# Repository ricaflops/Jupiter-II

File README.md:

# Jupiter-II
**Another Jupiter Ace computer clone**

## Main differences from the original Jupiter Ace
* Buffered composite video output
* Reset button
* Inversed video jumper selection
* Two screen pages and two character sets area (selectable at the video expansion connector)
* Reduced chip count with PLDs replacing several TTL logic
* Additional signals in expansion connectors

For more information on the original Jupiter Ace computer and an extensive software collection visit [The Jupiter Ace Archive](http://jupiter-ace.co.uk/)

## The Jupiter-II Expansion
See the [Jupiter-II Expansion](https://github.com/ricaflops/Jupiter-II-Expansion) project for adding:
- Video Colour
- Programmable Sound Generator
- 128K paged RAM
- Serial Interface
- FORTH vocabulary extension (Color, Memory Paging, Sound Generator, etc.)

# Jumper Settings

Inverse Video Jumper
- Jumper installed: Black text on white background (inversed)
- Jumper removed: White text on black background (default)

ROM image selection Jumper
- Jumper installed: Original Jupiter Ace 8K ROM image
- Jumper removed: Boot with the [Jupiter-II Expansion](https://github.com/ricaflops/Jupiter-II-Expansion)

The original Jupiter Ace 8K ROM image can be found at [The Jupiter Ace Archive](https://www.jupiter-ace.co.uk/).

# Connections

### Power Supply
Connect a 7.5Vdc to 9 Vdc x 1A power supply. Center pin is positive.

### A/V output
- pin 1: Audio Output (BEEP)
- pin 2: Common
- pin 3: Composite Video Output

The video standard is **60Hz NTSC** compatible but converting to 50Hz PAL by recoding the PLDs shall not be too difficult.

### Tape I/O
- pin 1: MIC output (for LOADing)
- pin 2: Common
- pin 3: EAR input (for SAVEing)

### Expansion
50 pin header connector (2x25 female).
Similar layout as the original Jupiter Ace with additional pins "-ROMSL" and "SPEAKER"

* pin 1:**GND** , pin 2:**GND**
* pin 3:**-INT** , pin 4:**GND**
* pin 5:**-NMI** , pin 6:**+9Vdc**
* pin 7:**-HALT** , pin 8:**+5Vdc**
* pin 9:**-MREQ** , pin 10:**-CLK**
* pin 11:**-IORQ** , pin 12:**A11**
* pin 13:**-RD** , pin 14:**A12**
* pin 15:**-WR** , pin 16:**A13**
* pin 17:**-BUSACK** , pin 18:**A14**
* pin 19:**-WAIT** , pin 20:**A15**
* pin 21:**-BUSRQ** , pin 22:**D4**
* pin 23:**-RESET** , pin 24:**D3**
* pin 25:**-M1** , pin 26:**D5**
* pin 27:**-RFSH** , pin 28:**A2**
* pin 29:**A6** , pin 30:**A10**
* pin 31:**A5** , pin 32:**A9**
* pin 33:**A4** , pin 34:**A8**
* pin 35:**A3** , pin 36:**A7**
* pin 37:**A1** , pin 38:**A0**
* pin 39:**D0** , pin 40:**D1**
* pin 41:**D2** , pin 42:**D6**
* pin 43:**D7** , pin 44:**-WE**
* pin 45:(n.c.) , pin 46:(n.c.)
* pin 47:**-ROMSL** , pin 48:**SPEAKER**
* pin 49:(n.c.) , pin 50:(n.c.)

(n.c.) means not connected

**-ROMSL** *(in)* Disables internal ROM chip when connected to +5V

**SPEAKER** *(out)* TTL level Speaker signal (BEEP)

### Video Expansion
30 pins header connector (2x15 female).
Similar layout as the original Jupiter Ace with some additional pins.

* pin 1:**VA3** , pin 2:**VA0**
* pin 3:**VA5** , pin 4:**VA4**
* pin 5:**VD2** , pin 6:**VD3**
* pin 7:**VD1** , pin 8:**VD4**
* pin 9:**VA6** , pin 10:**VD0**
* pin 11:**VA2** , pin 12:**VD7**
* pin 13:**-VRAMWR** , pin 14:**VD5**
* pin 15:**VA8** , pin 16:**VA7**
* pin 17:**VA9** , pin 18:**VA1**
* pin 19:**VD6** , pin 20:**-VLOAD**
* pin 21:**+5Vdc** , pin 22:**GND**
* pin 23:**-CPAGE** , pin 24:**-SPAGE**
* pin 25:**-SCRRAM** , pin 26:**-VSYNC**
* pin 27:**BORDER** , pin 28:**-HSYNC**
* pin 29:**LUMA** , pin 30:**BLANK**

**-VRAMWR** *(out)* Video RAM write enable

**-CPAGE** *(in)* Character Generator page selection

**-SPAGE** *(in)* Screen page selection

**-SCRRAM** *(out)* Screen RAM enabled

**-VSYNC** *(out)* Vertical Video Synch

**-HSYNC** *(out)* Horizontal Video Synch

**LUMA** *(out)* Video Luminance

**BLANK** *(out)* Video Blanking (retrace blanking)

## Tools used & file formats
* Designed with [Kicad](https://www.kicad.org/)
* Programmable Logic Devices coded in CUPL language (compiled with WinCupl available for free at [Microchip](https://www.microchip.com/))

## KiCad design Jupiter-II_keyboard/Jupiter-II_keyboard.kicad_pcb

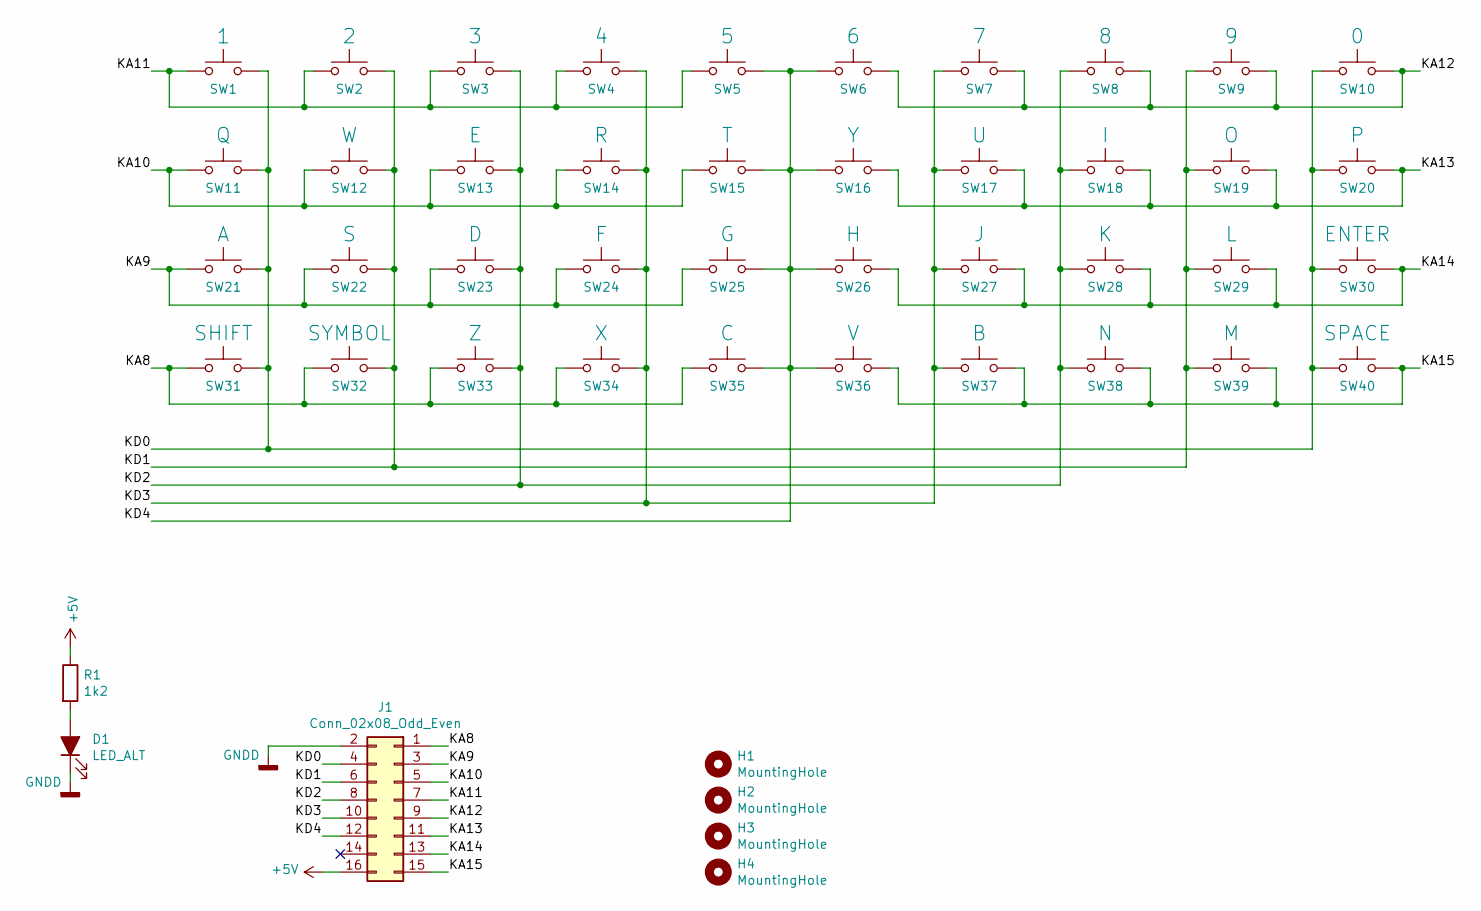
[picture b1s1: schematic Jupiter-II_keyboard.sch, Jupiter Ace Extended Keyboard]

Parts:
D1: LED_ALT; LED_1206_3216Metric_Pad1.42x1.75mm_HandSolder
H1, H2, H3, H4: MountingHole; MountingHole_3.2mm_M3
J1: Conn_02x08_Odd_Even; IDC-Header_2x08_P2.54mm_Vertical
R1: 1k2; R_0805_2012Metric_Pad1.15x1.40mm_HandSolder
SW1: 1; SW_PUSH_6mm
SW2: 2; SW_PUSH_6mm
SW3: 3; SW_PUSH_6mm
SW4: 4; SW_PUSH_6mm
SW5: 5; SW_PUSH_6mm
SW6: 6; SW_PUSH_6mm
SW7: 7; SW_PUSH_6mm
SW8: 8; SW_PUSH_6mm
SW9: 9; SW_PUSH_6mm
SW10: 0; SW_PUSH_6mm
SW11: Q; SW_PUSH_6mm
SW12: W; SW_PUSH_6mm
SW13: E; SW_PUSH_6mm
SW14: R; SW_PUSH_6mm
SW15: T; SW_PUSH_6mm
SW16: Y; SW_PUSH_6mm
SW17: U; SW_PUSH_6mm
SW18: I; SW_PUSH_6mm
SW19: O; SW_PUSH_6mm
SW20: P; SW_PUSH_6mm
SW21: A; SW_PUSH_6mm
SW22: S; SW_PUSH_6mm
SW23: D; SW_PUSH_6mm
SW24: F; SW_PUSH_6mm
SW25: G; SW_PUSH_6mm
SW26: H; SW_PUSH_6mm
SW27: J; SW_PUSH_6mm
SW28: K; SW_PUSH_6mm
SW29: L; SW_PUSH_6mm
SW30: ENTER; SW_PUSH_6mm
SW31: SHIFT; SW_PUSH_6mm
SW32: SYMBOL; SW_PUSH_6mm
SW33: Z; SW_PUSH_6mm
SW34: X; SW_PUSH_6mm
SW35: C; SW_PUSH_6mm
SW36: V; SW_PUSH_6mm
SW37: B; SW_PUSH_6mm
SW38: N; SW_PUSH_6mm
SW39: M; SW_PUSH_6mm
SW40: SPACE; SW_PUSH_6mm

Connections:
+5V: J1.16, R1.1
/KA8: J1.1, SW31.1, SW32.1, SW33.1, SW34.1, SW35.1
/KA9: J1.3, SW21.1, SW22.1, SW23.1, SW24.1, SW25.1
/KA10: J1.5, SW11.1, SW12.1, SW13.1, SW14.1, SW15.1
/KA11: J1.7, SW1.1, SW2.1, SW3.1, SW4.1, SW5.1
/KA12: J1.9, SW6.1, SW7.1, SW8.1, SW9.1, SW10.1
/KA13: J1.11, SW16.1, SW17.1, SW18.1, SW19.1, SW20.1
/KA14: J1.13, SW26.1, SW27.1, SW28.1, SW29.1, SW30.1
/KA15: J1.15, SW36.1, SW37.1, SW38.1, SW39.1, SW40.1
/KD0: J1.4, SW1.2, SW10.2, SW11.2, SW20.2, SW21.2, SW30.2, SW31.2, SW40.2
/KD1: J1.6, SW2.2, SW9.2, SW12.2, SW19.2, SW22.2, SW29.2, SW32.2, SW39.2
/KD2: J1.8, SW3.2, SW8.2, SW13.2, SW18.2, SW23.2, SW28.2, SW33.2, SW38.2
/KD3: J1.10, SW4.2, SW7.2, SW14.2, SW17.2, SW24.2, SW27.2, SW34.2, SW37.2
/KD4: J1.12, SW5.2, SW6.2, SW15.2, SW16.2, SW25.2, SW26.2, SW35.2, SW36.2
GNDD: D1.1 (K), J1.2
unnamed: D1.2 (A), R1.2

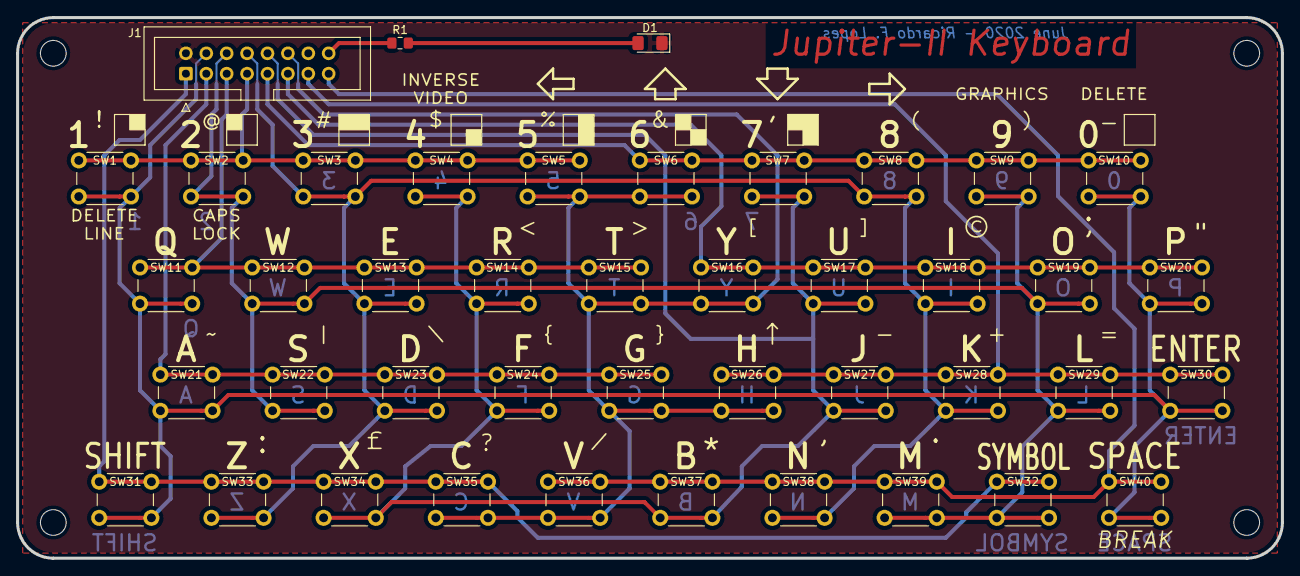
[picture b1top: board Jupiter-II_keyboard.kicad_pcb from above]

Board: 2 copper layers, 157.5 x 67.3 mm, 47 parts (0 on the bottom side), 16 nets.

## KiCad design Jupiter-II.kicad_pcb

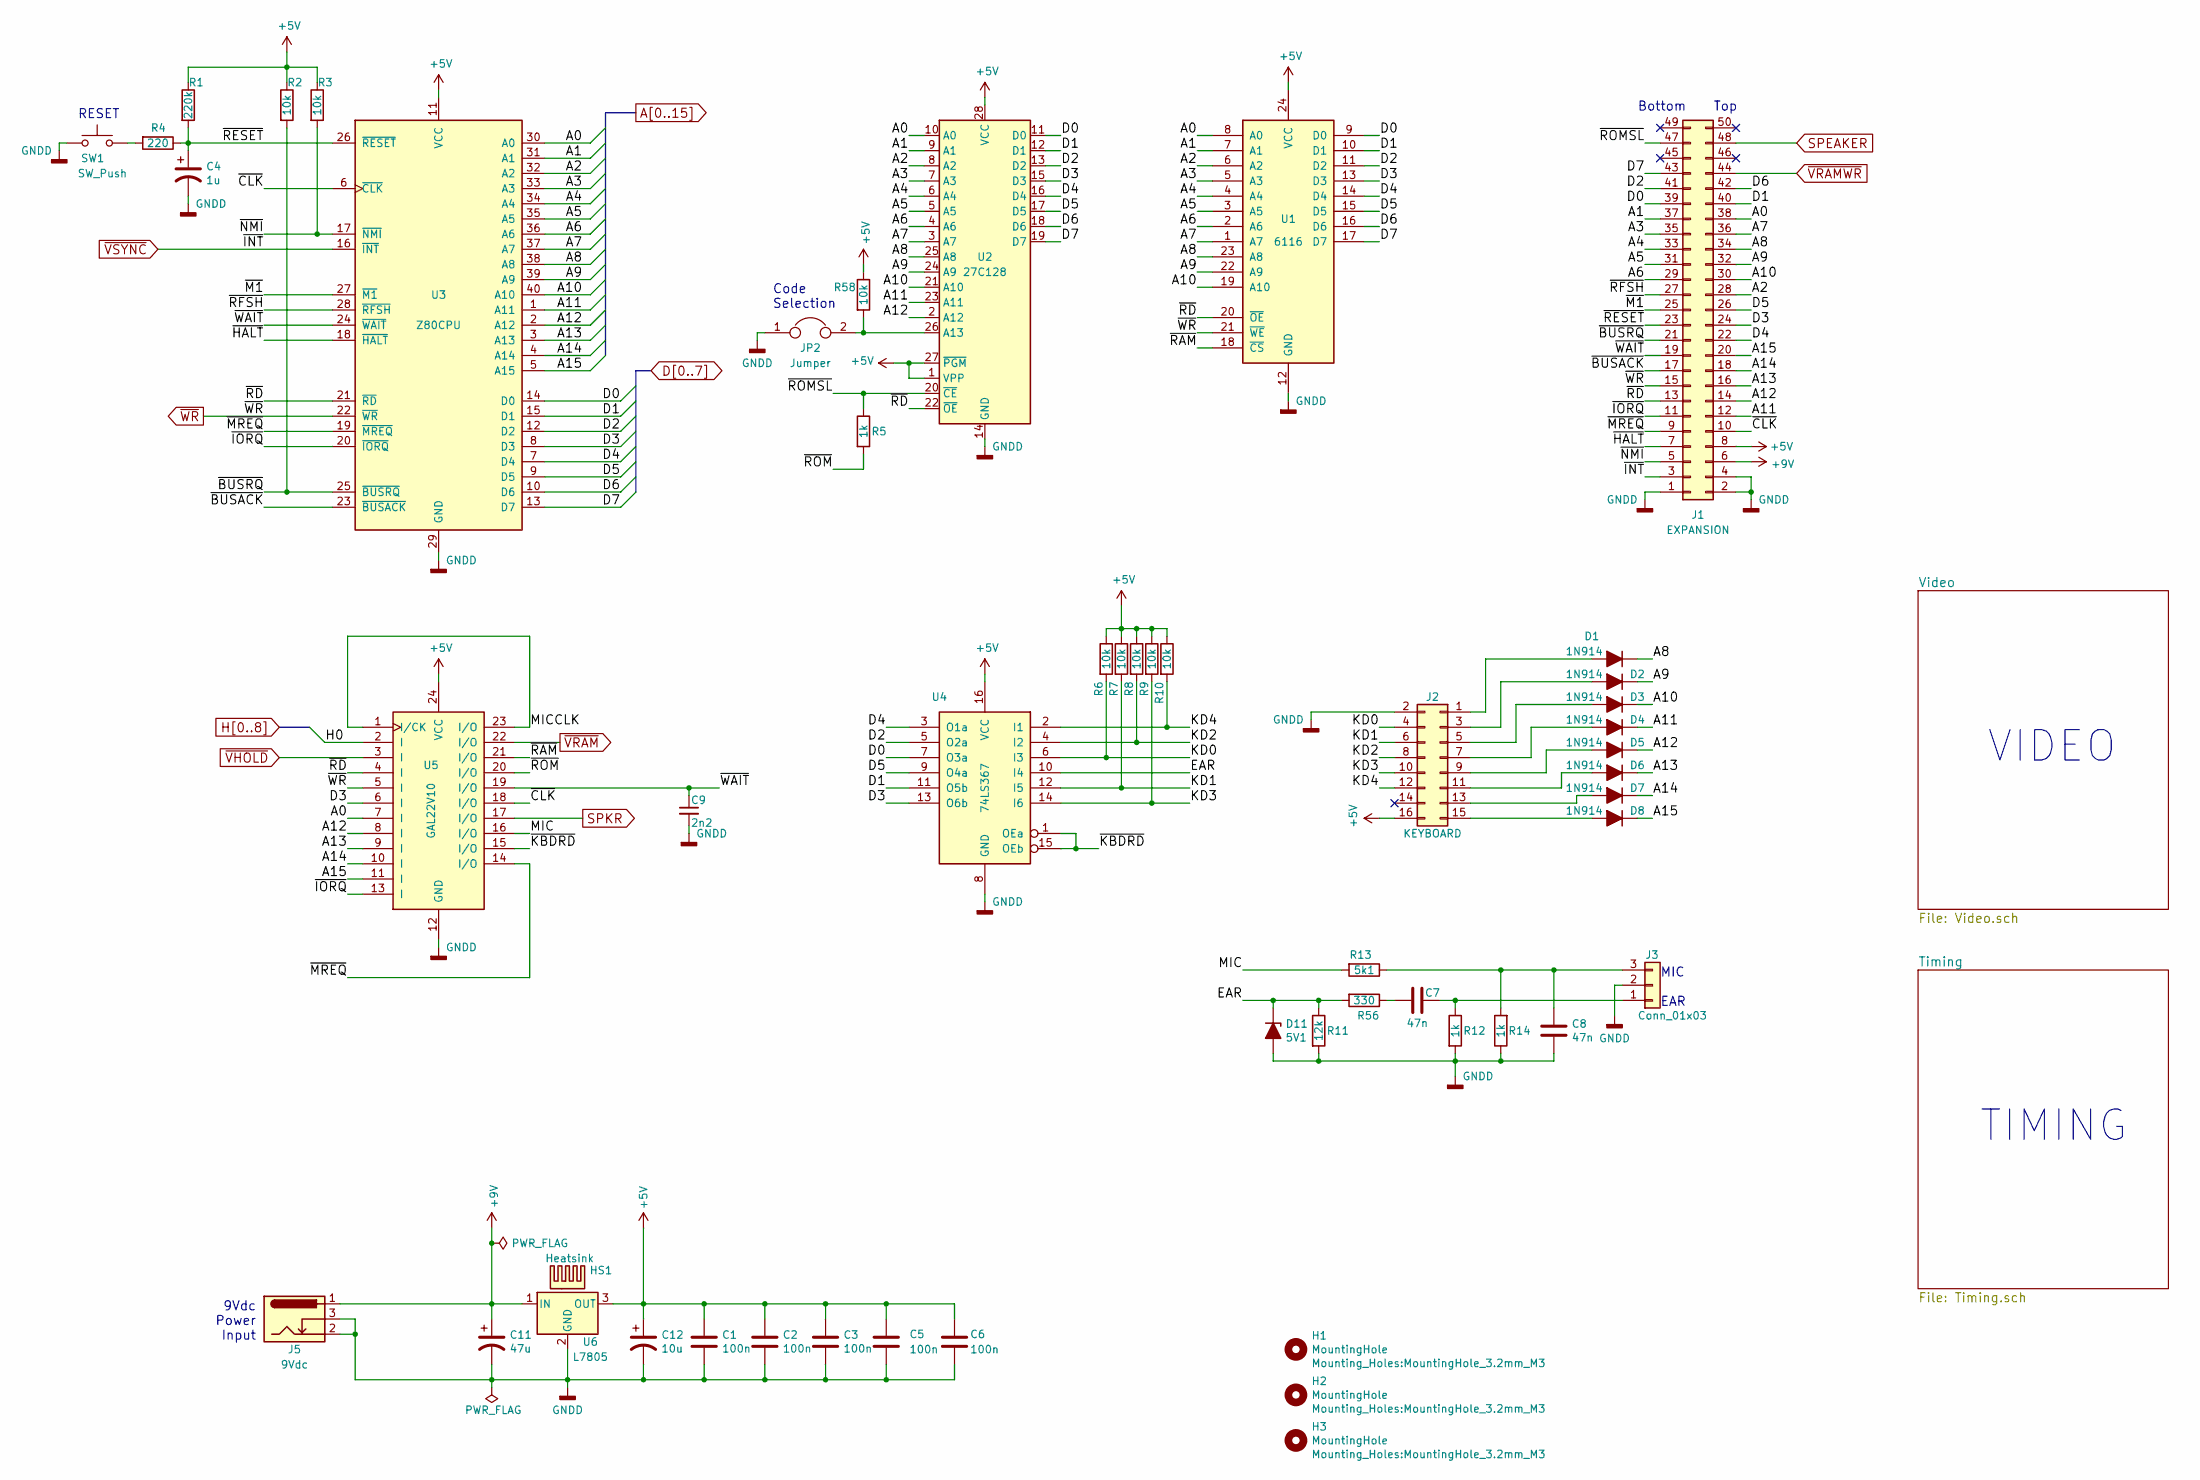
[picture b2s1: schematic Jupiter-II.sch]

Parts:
C1, C2, C3, C5, C6: 100n; C_Rect_L7.0mm_W2.5mm_P5.00mm
C4: 1u; CP_Radial_D6.3mm_P2.50mm
C7, C8: 47n; C_0805_2012Metric_Pad1.15x1.40mm_HandSolder
C9: 2n2; C_0805_2012Metric_Pad1.15x1.40mm_HandSolder
C11: 47u; CP_Radial_D6.3mm_P2.50mm
C12: 10u; CP_Radial_D6.3mm_P2.50mm
D1, D2, D3, D4, D5, D6, D7, D8: 1N914; D_DO-35_SOD27_P7.62mm_Horizontal
D11: 5V1; D_DO-35_SOD27_P2.54mm_Vertical_KathodeUp
H1, H2, H3: MountingHole; MountingHole_3.2mm_M3
HS1: Heatsink; Heatsink_35x12mm_2xFixation1.5mm
J1: EXPANSION; Socket_Strip_Straight_2x25_Pitch2.54mm
J2: KEYBOARD; Multicomp_MC9A12-1634_2x08x2.54mm_Straight
J3: Conn_01x03; Pin_Header_Angled_1x03_Pitch2.54mm
J5: 9Vdc; BarrelJack_Horizontal
JP2: Jumper; PinHeader_1x02_P2.54mm_Vertical
R1: 220k; R_0805_2012Metric_Pad1.15x1.40mm_HandSolder
R2, R3, R6, R7, R8, R9, R10, R58: 10k; R_0805_2012Metric_Pad1.15x1.40mm_HandSolder
R4: 220; R_0805_2012Metric_Pad1.15x1.40mm_HandSolder
R5, R12, R14: 1k; R_0805_2012Metric_Pad1.15x1.40mm_HandSolder
R11: 12k; R_0805_2012Metric_Pad1.15x1.40mm_HandSolder
R13: 5k1; R_0805_2012Metric_Pad1.15x1.40mm_HandSolder
R56: 330; R_0805_2012Metric_Pad1.15x1.40mm_HandSolder
SW1: SW_Push; SW_Tactile_SPST_Angled_PTS645Vx58-2LFS
U1: 6116; DIP-24_W15.24mm_Socket
U2: 27C128; DIP-28_W15.24mm
U3: Z80CPU; DIP-40_W15.24mm_Socket
U4: 74LS367; DIP-16_W7.62mm
U5: GAL22V10; DIP-24_W7.62mm_Socket
U6: L7805; TO-220-3_Vertical

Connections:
+5V: C1.1, C2.1, C3.1, C5.1, C6.1, C12.1, J1.8, J2.16, R1.1, R2.1, R3.1, R6.1, R7.1, R8.1, R9.1, R10.1, R58.1, U1.24 (VCC), U2.1 (VPP), U2.27 (~PGM), U2.28 (VCC), U3.11 (VCC), U4.16 (VCC), U5.24 (VCC), U6.3 (OUT); also elsewhere on the board
+9V: C11.1, J1.6, J5.1, U6.1 (IN)
/EAR: D11.1 (K), R11.1, R56.2, U4.10 (I4)
/KD0: J2.4, R6.2, U4.6 (I3)
/KD1: J2.6, R7.2, U4.12 (I5)
/KD2: J2.8, R8.2, U4.4 (I2)
/KD3: J2.10, R9.2, U4.14 (I6)
/KD4: J2.12, R10.2, U4.2 (I1)
/MIC: R13.2, U5.16 (I/O)
/MICCLK: U5.1 (I/CK), U5.23 (I/O)
/~BUSACK: J1.17, U3.23 (~BUSACK~)
/~BUSRQ: J1.21, R2.2, U3.25 (~BUSRQ~)
/~CLK: J1.10, U3.6 (~CLK~), U5.18 (I/O)
/~HALT: J1.7, U3.18 (~HALT~)
/~IORQ: J1.11, U3.20 (~IORQ~), U5.13 (I)
/~KBDRD: U4.1 (OEa), U4.15 (OEb), U5.15 (I/O)
/~M1: J1.25, U3.27 (~M1~)
/~MREQ: J1.9, U3.19 (~MREQ~), U5.14 (I/O)
/~NMI: J1.5, R3.2, U3.17 (~NMI~)
/~RAM: U1.18 (~CS), U5.21 (I/O)
/~RD: J1.13, U1.20 (~OE), U2.22 (~OE), U3.21 (~RD~), U5.4 (I)
/~RESET: C4.1, J1.23, R1.2, R4.1, U3.26 (~RESET~)
/~RFSH: J1.27, U3.28 (~RFSH~)
/~ROM: R5.2, U5.20 (I/O)
/~ROMSL: J1.47, R5.1, U2.20 (~CE)
/~WAIT: C9.1, J1.19, U3.24 (~WAIT~), U5.19 (I/O)
A0: J1.38, U1.8 (A0), U2.10 (A0), U3.30 (A0), U5.7 (I); also elsewhere on the board
A1: J1.37, U1.7 (A1), U2.9 (A1), U3.31 (A1); also elsewhere on the board
A2: J1.28, U1.6 (A2), U2.8 (A2), U3.32 (A2); also elsewhere on the board
A3: J1.35, U1.5 (A3), U2.7 (A3), U3.33 (A3); also elsewhere on the board
A4: J1.33, U1.4 (A4), U2.6 (A4), U3.34 (A4); also elsewhere on the board
A5: J1.31, U1.3 (A5), U2.5 (A5), U3.35 (A5); also elsewhere on the board
A6: J1.29, U1.2 (A6), U2.4 (A6), U3.36 (A6); also elsewhere on the board
A7: J1.36, U1.1 (A7), U2.3 (A7), U3.37 (A7); also elsewhere on the board
A8: D1.1 (K), J1.34, U1.23 (A8), U2.25 (A8), U3.38 (A8); also elsewhere on the board
A9: D2.1 (K), J1.32, U1.22 (A9), U2.24 (A9), U3.39 (A9); also elsewhere on the board
A10: D3.1 (K), J1.30, U1.19 (A10), U2.21 (A10), U3.40 (A10); also elsewhere on the board
A11: D4.1 (K), J1.12, U2.23 (A11), U3.1 (A11); also elsewhere on the board
A12: D5.1 (K), J1.14, U2.2 (A12), U3.2 (A12), U5.8 (I)
A13: D6.1 (K), J1.16, U3.3 (A13), U5.9 (I)
A14: D7.1 (K), J1.18, U3.4 (A14), U5.10 (I)
A15: D8.1 (K), J1.20, U3.5 (A15), U5.11 (I)
D0: J1.39, U1.9 (D0), U2.11 (D0), U3.14 (D0), U4.7 (O3a); also elsewhere on the board
D1: J1.40, U1.10 (D1), U2.12 (D1), U3.15 (D1), U4.11 (O5b); also elsewhere on the board
D2: J1.41, U1.11 (D2), U2.13 (D2), U3.12 (D2), U4.5 (O2a); also elsewhere on the board
D3: J1.24, U1.13 (D3), U2.15 (D3), U3.8 (D3), U4.13 (O6b), U5.6 (I); also elsewhere on the board
D4: J1.22, U1.14 (D4), U2.16 (D4), U3.7 (D4), U4.3 (O1a); also elsewhere on the board
D5: J1.26, U1.15 (D5), U2.17 (D5), U3.9 (D5), U4.9 (O4a); also elsewhere on the board
D6: J1.42, U1.16 (D6), U2.18 (D6), U3.10 (D6); also elsewhere on the board
D7: J1.43, U1.17 (D7), U2.19 (D7), U3.13 (D7); also elsewhere on the board
GNDD: C1.2, C2.2, C3.2, C4.2, C5.2, C6.2, C8.2, C9.2, C11.2, C12.2, D11.2 (A), J1.1, J1.2, J1.4, J2.2, J3.2, J5.2, J5.3, JP2.1, R11.2, R12.2, R14.1, SW1.1, U1.12 (GND), U2.14 (GND), U3.29 (GND), U4.8 (GND), U5.12 (GND), U6.2 (GND); also elsewhere on the board
H0: U5.2 (I); also elsewhere on the board
unnamed: C7.1, J3.1, R12.1
unnamed: C7.2, R56.1
unnamed: C8.1, J3.3, R13.1, R14.2
unnamed: D1.2 (A), J2.1
unnamed: D2.2 (A), J2.3
unnamed: D3.2 (A), J2.5
unnamed: D4.2 (A), J2.7
unnamed: D5.2 (A), J2.9
unnamed: D6.2 (A), J2.11
unnamed: D7.2 (A), J2.13
unnamed: D8.2 (A), J2.15
unnamed: JP2.2, R58.2, U2.26 (A13)
unnamed: R4.2, SW1.2
SPEAKER: J1.48; also elsewhere on the board
SPKR: U5.17 (I/O); also elsewhere on the board
~VHOLD: U5.3 (I); also elsewhere on the board
~VRAM: U5.22 (I/O); also elsewhere on the board
~VRAMWR: J1.44; also elsewhere on the board
~VSYNC: J1.3, U3.16 (~INT~); also elsewhere on the board
~WR: J1.15, U1.21 (~WE), U3.22 (~WR~), U5.5 (I); also elsewhere on the board

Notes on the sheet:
RESET
TIMING
VIDEO
Bottom Top
9Vdc Power Input
MIC EAR
Code Selection

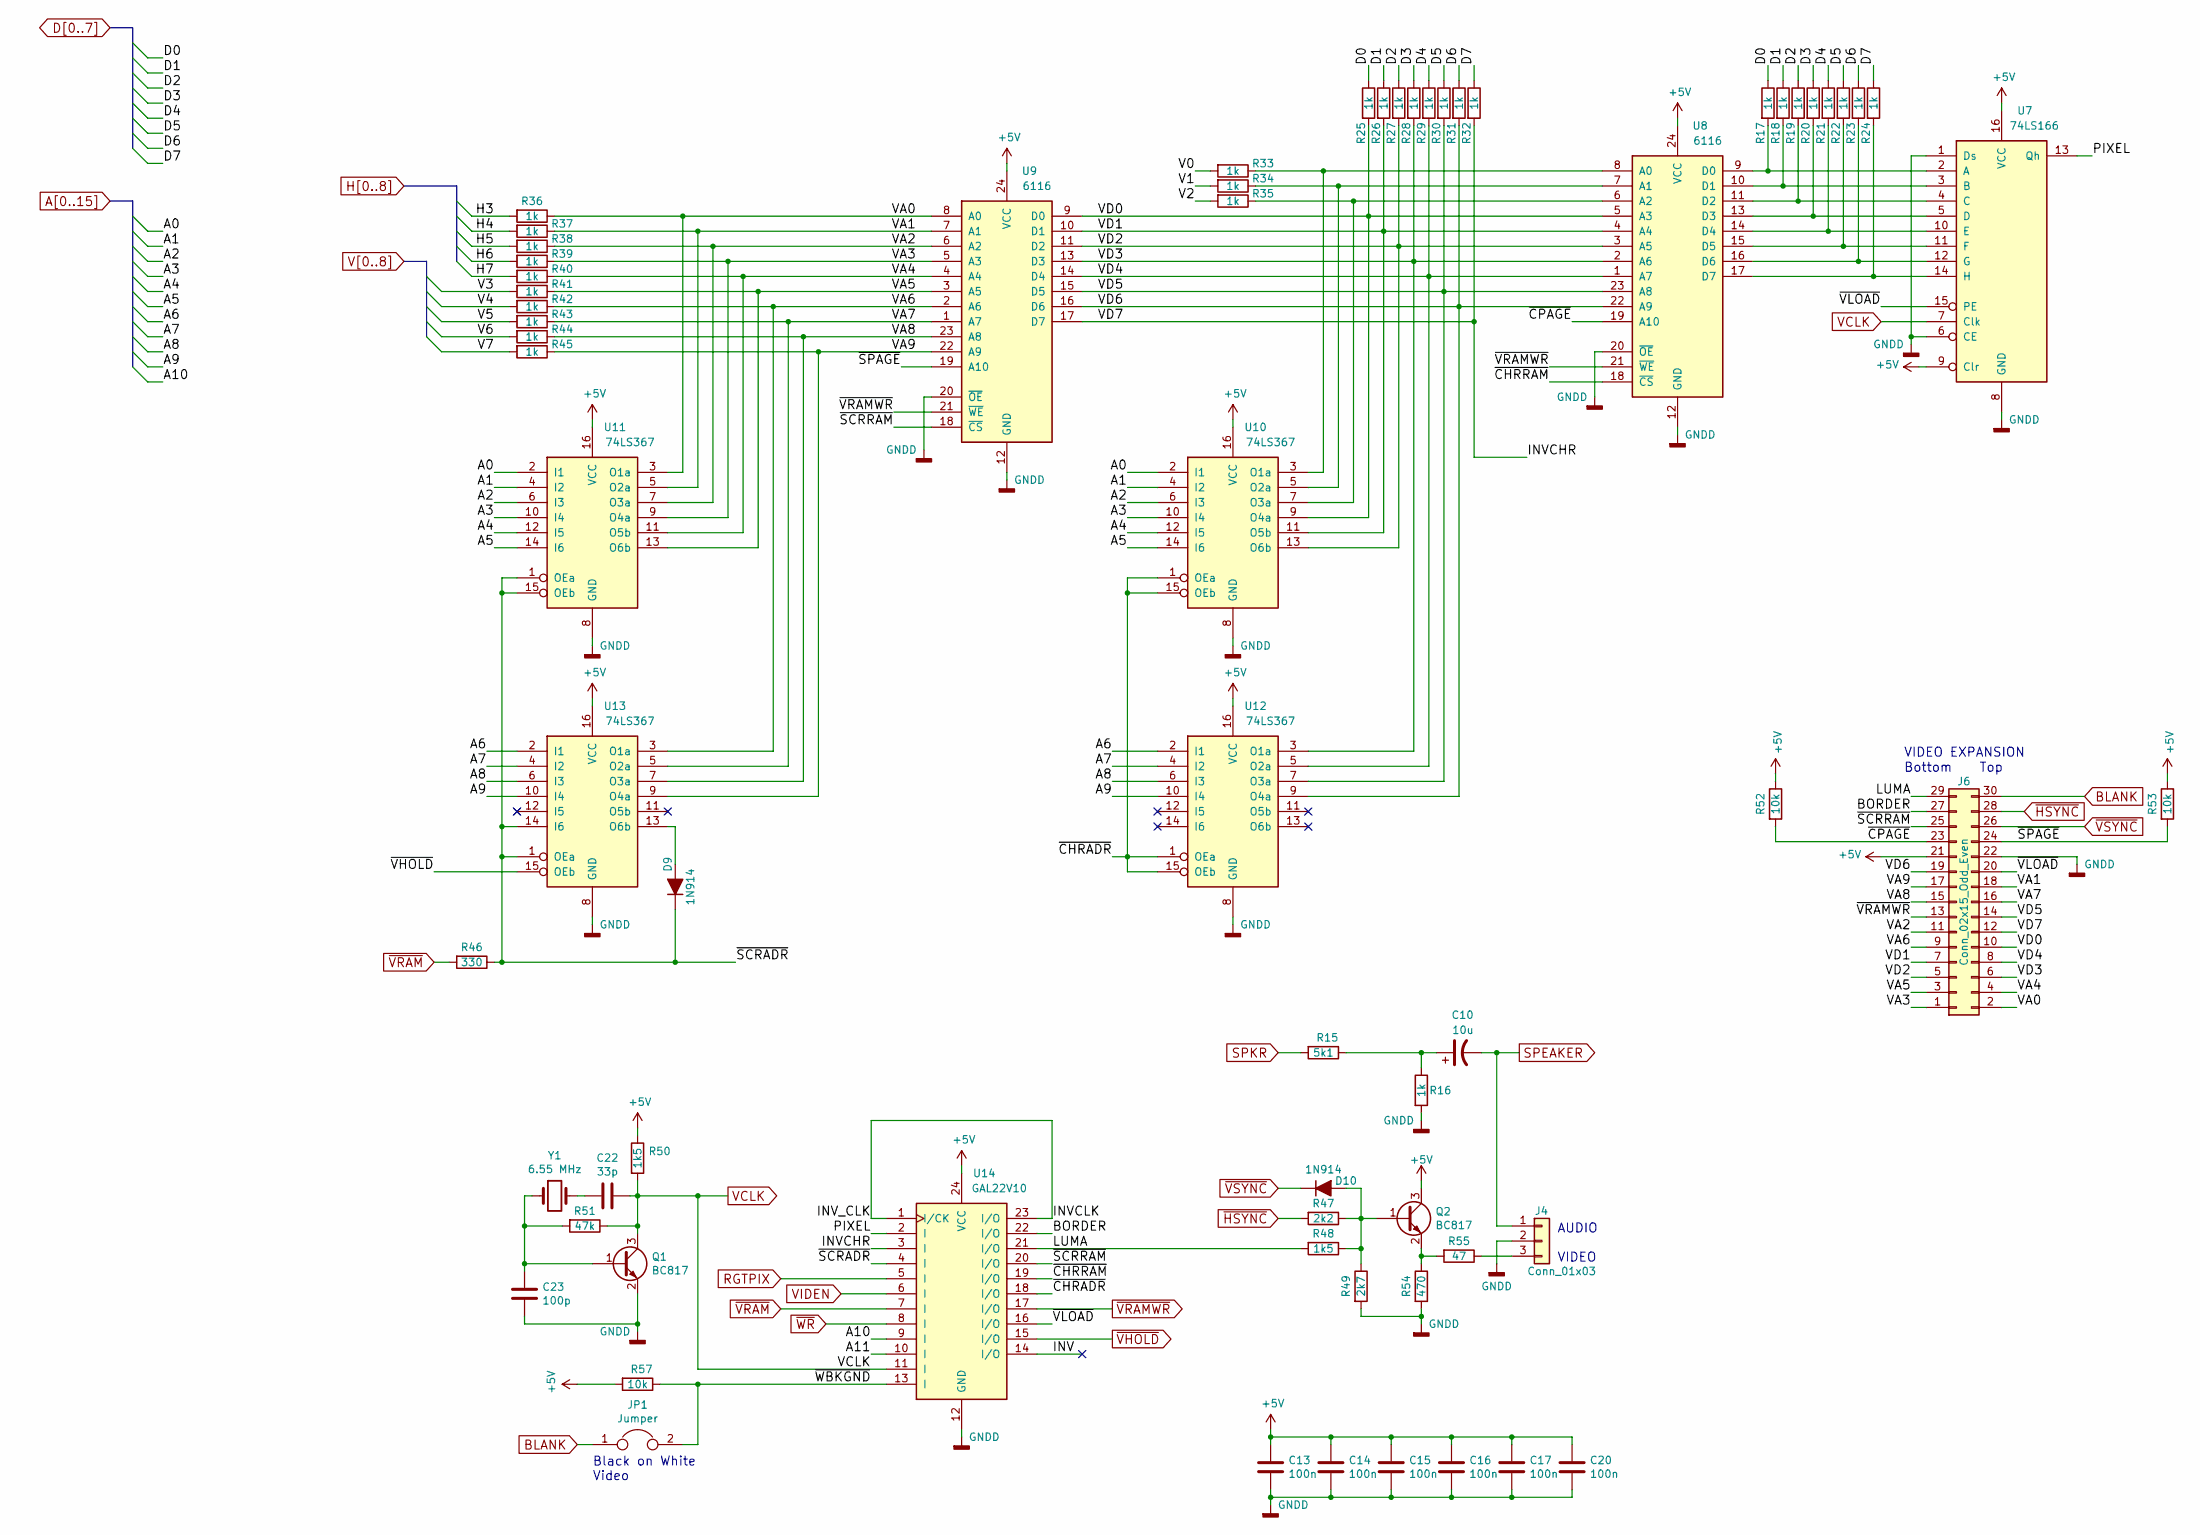
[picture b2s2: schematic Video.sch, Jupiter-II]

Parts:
C10: 10u; CP_Radial_D6.3mm_P2.50mm
C13, C14, C15, C16, C17, C20: 100n; C_Rect_L7.0mm_W2.5mm_P5.00mm
C22: 33p; C_0805_2012Metric_Pad1.15x1.40mm_HandSolder
C23: 100p; C_0805_2012Metric_Pad1.15x1.40mm_HandSolder
D9, D10: 1N914; D_DO-35_SOD27_P7.62mm_Horizontal
J4: Conn_01x03; Molex_KK-6410-03_03x2.54mm_Straight
J6: Conn_02x15_Odd_Even; Socket_Strip_Straight_2x15_Pitch2.54mm
JP1: Jumper; Pin_Header_Straight_1x02_Pitch2.54mm
Q1, Q2: BC817; SOT-23
R15: 5k1; R_0805_2012Metric_Pad1.15x1.40mm_HandSolder
R16, R17, R18, R19, R20, R21, R22, R23, R24, R25, R26, R27, R28, R29, R30, R31, R32, R33, R34, R35, R36, R37, R38, R39, R40, R41, R42, R43, R44, R45: 1k; R_0805_2012Metric_Pad1.15x1.40mm_HandSolder
R46: 330; R_0805_2012Metric_Pad1.15x1.40mm_HandSolder
R47: 2k2; R_0805_2012Metric_Pad1.15x1.40mm_HandSolder
R48, R50: 1k5; R_0805_2012Metric_Pad1.15x1.40mm_HandSolder
R49: 2k7; R_0805_2012Metric_Pad1.15x1.40mm_HandSolder
R51: 47k; R_0805_2012Metric_Pad1.15x1.40mm_HandSolder
R52, R53, R57: 10k; R_0805_2012Metric_Pad1.15x1.40mm_HandSolder
R54: 470; R_0805_2012Metric_Pad1.15x1.40mm_HandSolder
R55: 47; R_0805_2012Metric_Pad1.15x1.40mm_HandSolder
U7: 74LS166; DIP-16_W7.62mm
U8, U9: 6116; DIP-24_W15.24mm_Socket
U10, U11, U12, U13: 74LS367; DIP-16_W7.62mm
U14: GAL22V10; DIP-24_W7.62mm_Socket
Y1: 6.55 MHz; Crystal_HC18-U_Vertical

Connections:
+5V: C13.1, C14.1, C15.1, C16.1, C17.1, C20.1, J6.21, Q2.3 (C), R50.1, R52.1, R53.1, R57.2, U7.9 (Clr), U7.16 (VCC), U8.24 (VCC), U9.24 (VCC), U10.16 (VCC), U11.16 (VCC), U12.16 (VCC), U13.16 (VCC), U14.24 (VCC); also elsewhere on the board
/Video/BORDER: J6.27, U14.22 (I/O)
/Video/INV: U14.14 (I/O)
/Video/INVCHR: J6.12, R32.2, U9.17 (D7), U14.3 (I)
/Video/INVCLK: U14.1 (I/CK), U14.23 (I/O)
/Video/LUMA: J6.29, R48.2, U14.21 (I/O)
/Video/PIXEL: U7.13 (Qh), U14.2 (I)
/Video/VA0: J6.2, R36.1, U9.8 (A0), U11.3 (O1a)
/Video/VA1: J6.18, R37.1, U9.7 (A1), U11.5 (O2a)
/Video/VA2: J6.11, R38.1, U9.6 (A2), U11.7 (O3a)
/Video/VA3: J6.1, R39.1, U9.5 (A3), U11.9 (O4a)
/Video/VA4: J6.4, R40.1, U9.4 (A4), U11.11 (O5b)
/Video/VA5: J6.3, R41.1, U9.3 (A5), U11.13 (O6b)
/Video/VA6: J6.9, R42.1, U9.2 (A6), U13.3 (O1a)
/Video/VA7: J6.16, R43.1, U9.1 (A7), U13.5 (O2a)
/Video/VA8: J6.15, R44.1, U9.23 (A8), U13.7 (O3a)
/Video/VA9: J6.17, R45.1, U9.22 (A9), U13.9 (O4a)
/Video/VD0: J6.10, R25.2, U8.5 (A3), U9.9 (D0), U10.9 (O4a)
/Video/VD1: J6.7, R26.2, U8.4 (A4), U9.10 (D1), U10.11 (O5b)
/Video/VD2: J6.5, R27.2, U8.3 (A5), U9.11 (D2), U10.13 (O6b)
/Video/VD3: J6.6, R28.2, U8.2 (A6), U9.13 (D3), U12.3 (O1a)
/Video/VD4: J6.8, R29.2, U8.1 (A7), U9.14 (D4), U12.5 (O2a)
/Video/VD5: J6.14, R30.2, U8.23 (A8), U9.15 (D5), U12.7 (O3a)
/Video/VD6: J6.19, R31.2, U8.22 (A9), U9.16 (D6), U12.9 (O4a)
/Video/~CHRADR: U10.1 (OEa), U10.15 (OEb), U12.1 (OEa), U12.15 (OEb), U14.18 (I/O)
/Video/~CHRRAM: U8.18 (~CS), U14.19 (I/O)
/Video/~CPAGE: J6.23, R52.2, U8.19 (A10)
/Video/~SCRADR: D9.1 (K), R46.1, U11.1 (OEa), U11.15 (OEb), U13.1 (OEa), U13.14 (I6), U14.4 (I)
/Video/~SCRRAM: J6.25, U9.18 (~CS), U14.20 (I/O)
/Video/~SPAGE: J6.24, R53.2, U9.19 (A10)
/Video/~VLOAD: J6.20, U7.15 (PE), U14.16 (I/O)
/Video/~WBKGND: JP1.2, R57.1, U14.13 (I)
A0: U10.2 (I1), U11.2 (I1); also elsewhere on the board
A1: U10.4 (I2), U11.4 (I2); also elsewhere on the board
A2: U10.6 (I3), U11.6 (I3); also elsewhere on the board
A3: U10.10 (I4), U11.10 (I4); also elsewhere on the board
A4: U10.12 (I5), U11.12 (I5); also elsewhere on the board
A5: U10.14 (I6), U11.14 (I6); also elsewhere on the board
A6: U12.2 (I1), U13.2 (I1); also elsewhere on the board
A7: U12.4 (I2), U13.4 (I2); also elsewhere on the board
A8: U12.6 (I3), U13.6 (I3); also elsewhere on the board
A9: U12.10 (I4), U13.10 (I4); also elsewhere on the board
A10: U14.9 (I); also elsewhere on the board
A11: U14.10 (I); also elsewhere on the board
BLANK: J6.30, JP1.1; also elsewhere on the board
D0: R17.1, R25.1; also elsewhere on the board
D1: R18.1, R26.1; also elsewhere on the board
D2: R19.1, R27.1; also elsewhere on the board
D3: R20.1, R28.1; also elsewhere on the board
D4: R21.1, R29.1; also elsewhere on the board
D5: R22.1, R30.1; also elsewhere on the board
D6: R23.1, R31.1; also elsewhere on the board
D7: R24.1, R32.1; also elsewhere on the board
GNDD: C13.2, C14.2, C15.2, C16.2, C17.2, C20.2, C23.2, J4.2, J6.22, Q1.2 (E), R16.2, R49.2, R54.2, U7.1 (Ds), U7.6 (CE), U7.8 (GND), U8.12 (GND), U8.20 (~OE), U9.12 (GND), U9.20 (~OE), U10.8 (GND), U11.8 (GND), U12.8 (GND), U13.8 (GND), U14.12 (GND); also elsewhere on the board
H3: R36.2; also elsewhere on the board
H4: R37.2; also elsewhere on the board
H5: R38.2; also elsewhere on the board
H6: R39.2; also elsewhere on the board
H7: R40.2; also elsewhere on the board
unnamed: C10.1, R15.1, R16.1
unnamed: C22.2, Y1.2
unnamed: C23.1, Q1.1 (B), R51.2, Y1.1
unnamed: D9.2 (A), U13.13 (O6b)
unnamed: D10.2 (A), Q2.1 (B), R47.1, R48.1, R49.1
unnamed: J4.3, R55.1
unnamed: Q2.2 (E), R54.1, R55.2
unnamed: R17.2, U7.2 (A), U8.9 (D0)
unnamed: R18.2, U7.3 (B), U8.10 (D1)
unnamed: R19.2, U7.4 (C), U8.11 (D2)
unnamed: R20.2, U7.5 (D), U8.13 (D3)
unnamed: R21.2, U7.10 (E), U8.14 (D4)
unnamed: R22.2, U7.11 (F), U8.15 (D5)
unnamed: R23.2, U7.12 (G), U8.16 (D6)
unnamed: R24.2, U7.14 (H), U8.17 (D7)
unnamed: R33.1, U8.8 (A0), U10.3 (O1a)
unnamed: R34.1, U8.7 (A1), U10.5 (O2a)
unnamed: R35.1, U8.6 (A2), U10.7 (O3a)
RGTPIX: U14.5 (I); also elsewhere on the board
SPEAKER: C10.2, J4.1; also elsewhere on the board
SPKR: R15.2; also elsewhere on the board
V0: R33.2; also elsewhere on the board
V1: R34.2; also elsewhere on the board
V2: R35.2; also elsewhere on the board
V3: R41.2; also elsewhere on the board
V4: R42.2; also elsewhere on the board
V5: R43.2; also elsewhere on the board
V6: R44.2; also elsewhere on the board
V7: R45.2; also elsewhere on the board
VCLK: C22.1, Q1.3 (C), R50.2, R51.1, U7.7 (Clk), U14.11 (I); also elsewhere on the board
VIDEN: U14.6 (I); also elsewhere on the board
~HSYNC: J6.28, R47.2; also elsewhere on the board
~VHOLD: U13.15 (OEb), U14.15 (I/O); also elsewhere on the board
~VRAM: R46.2, U14.7 (I); also elsewhere on the board
~VRAMWR: J6.13, U8.21 (~WE), U9.21 (~WE), U14.17 (I/O); also elsewhere on the board
~VSYNC: D10.1 (K), J6.26; also elsewhere on the board
~WR: U14.8 (I); also elsewhere on the board

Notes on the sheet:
AUDIO VIDEO
Bottom Top
VIDEO EXPANSION
Black on White Video

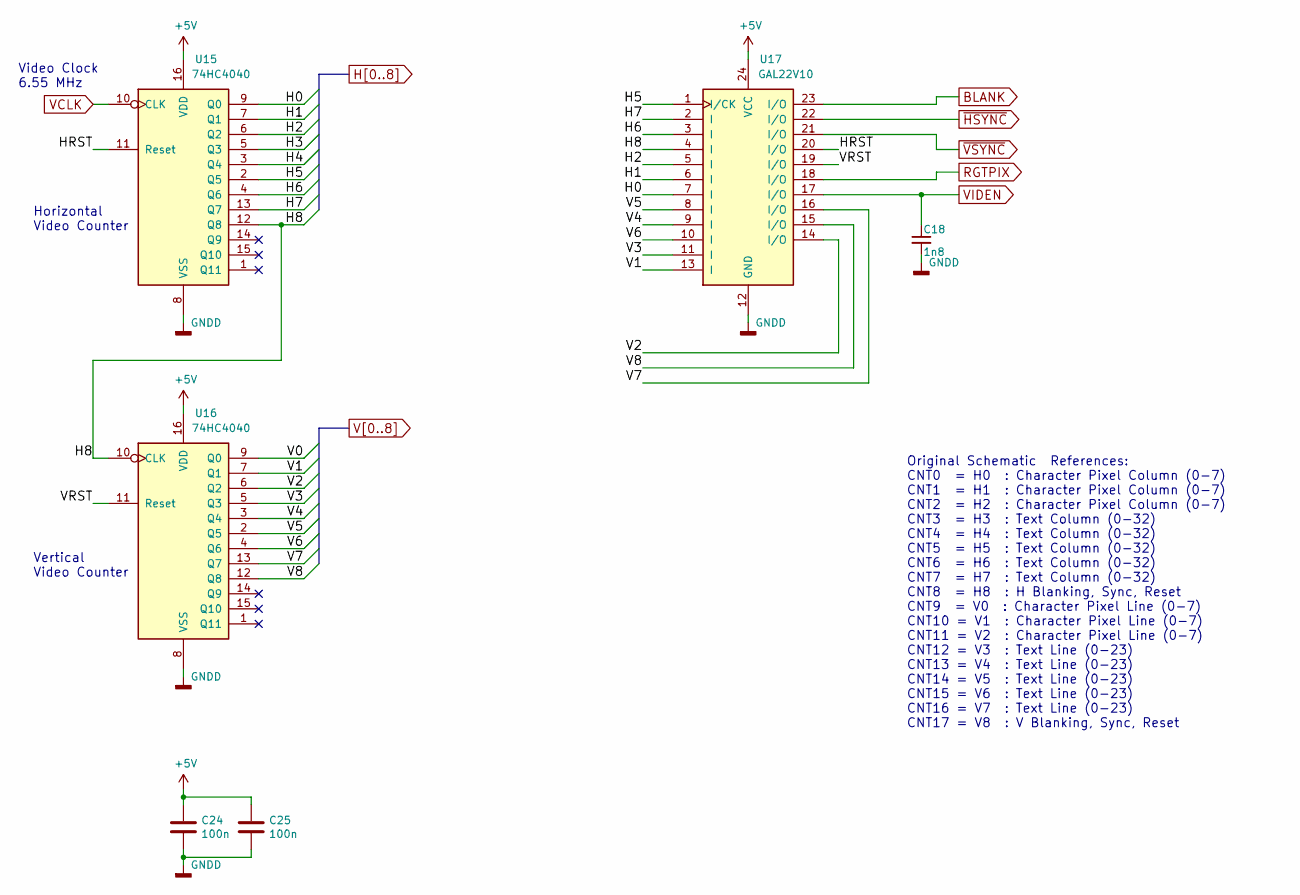
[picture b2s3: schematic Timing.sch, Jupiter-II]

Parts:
C18: 1n8; C_0805_2012Metric_Pad1.15x1.40mm_HandSolder
C24, C25: 100n; C_Rect_L7.0mm_W2.5mm_P5.00mm
U15, U16: 74HC4040; DIP-16_W7.62mm
U17: GAL22V10; DIP-24_W7.62mm_Socket

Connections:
+5V: C24.1, C25.1, U15.16 (VDD), U16.16 (VDD), U17.24 (VCC); also elsewhere on the board
/Timing/HRST: U15.11 (Reset), U17.20 (I/O)
/Timing/VRST: U16.11 (Reset), U17.19 (I/O)
BLANK: U17.23 (I/O); also elsewhere on the board
GNDD: C18.2, C24.2, C25.2, U15.8 (VSS), U16.8 (VSS), U17.12 (GND); also elsewhere on the board
H0: U15.9 (Q0), U17.7 (I); also elsewhere on the board
H1: U15.7 (Q1), U17.6 (I)
H2: U15.6 (Q2), U17.5 (I)
H3: U15.5 (Q3); also elsewhere on the board
H4: U15.3 (Q4); also elsewhere on the board
H5: U15.2 (Q5), U17.1 (I/CK); also elsewhere on the board
H6: U15.4 (Q6), U17.3 (I); also elsewhere on the board
H7: U15.13 (Q7), U17.2 (I); also elsewhere on the board
H8: U15.12 (Q8), U16.10 (CLK), U17.4 (I)
RGTPIX: U17.18 (I/O); also elsewhere on the board
V0: U16.9 (Q0); also elsewhere on the board
V1: U16.7 (Q1), U17.13 (I); also elsewhere on the board
V2: U16.6 (Q2), U17.14 (I/O); also elsewhere on the board
V3: U16.5 (Q3), U17.11 (I); also elsewhere on the board
V4: U16.3 (Q4), U17.9 (I); also elsewhere on the board
V5: U16.2 (Q5), U17.8 (I); also elsewhere on the board
V6: U16.4 (Q6), U17.10 (I); also elsewhere on the board
V7: U16.13 (Q7), U17.16 (I/O); also elsewhere on the board
V8: U16.12 (Q8), U17.15 (I/O)
VCLK: U15.10 (CLK); also elsewhere on the board
VIDEN: C18.1, U17.17 (I/O); also elsewhere on the board
~HSYNC: U17.22 (I/O); also elsewhere on the board
~VSYNC: U17.21 (I/O); also elsewhere on the board

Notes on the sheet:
Video Clock 6.55 MHz
Horizontal Video Counter
Vertical Video Counter
Original Schematic References: CNT0 = H0 : Character Pixel Column (0-7) CNT1 = H1 : Character Pixel Column (0-7) CNT2 = H2 : Character Pixel Column (0-7) CNT3 = H3 : Text Column (0-32) CNT4 = H4 : Text Column (0-32) CNT5 = H5 : Text Column (0-32) CNT6 = H6 : Text Column (0-32) CNT7 = H7 : Text Colu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

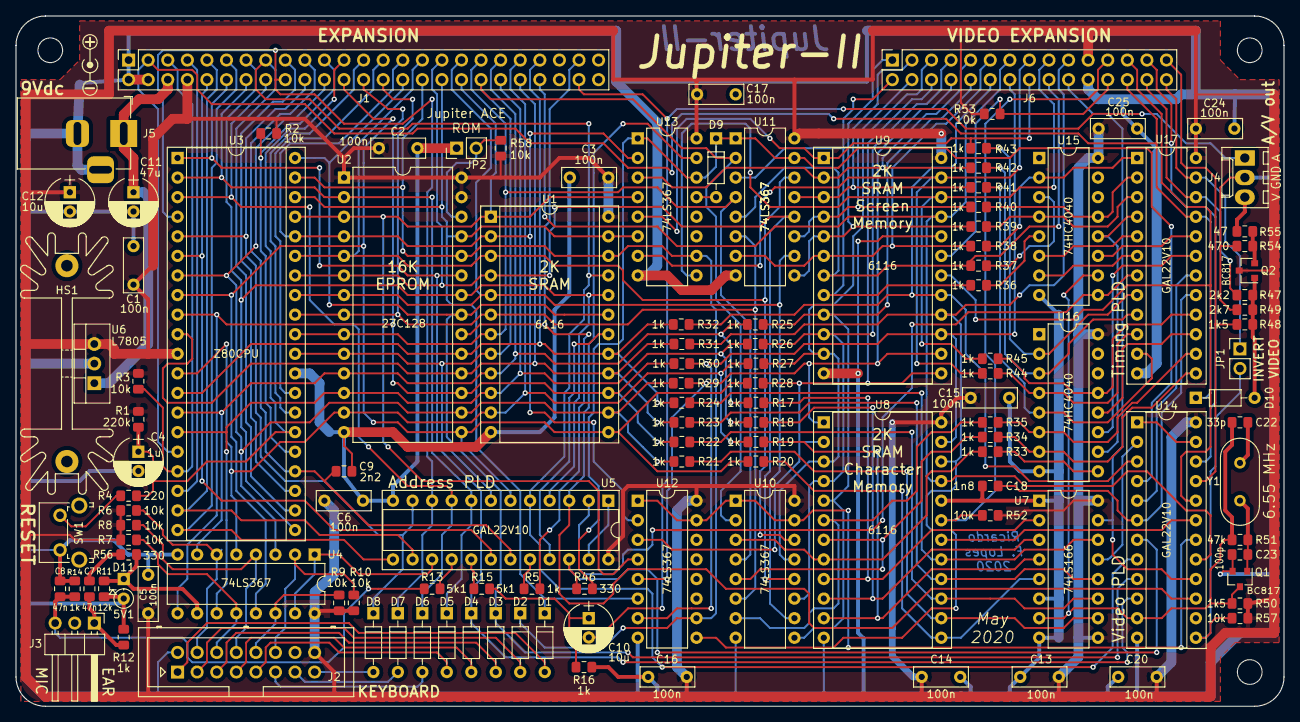
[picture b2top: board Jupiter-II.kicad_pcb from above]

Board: 2 copper layers, 164.5 x 89.5 mm, 126 parts (0 on the bottom side), 144 nets.

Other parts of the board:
REF01: Symbol_Barrel_Polarity

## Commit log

2020-04-06 Initial Release
2020-05-11 Making it work
    Corrected U4 (74LS367) swapped i/o lines
    Improved video output circuit
    Optimized audio circuit component values
    Modified Mic output circuit
    Corrected Silk screen swapped labels "R1" and "R3"
2020-05-11 working PLD code
2020-05-11 Netlist update
2020-05-11 Gerbers reflecting updated PCB layout
2020-05-14 Fix audio output
2020-05-15 Keyboard
2020-05-15 Better video image centering
2020-05-17 Inverted video option
2020-05-17 Silk screen layer updated
2020-05-17 Better horizontal blank timing
    No front porch blanking leading H-sync pulse, keeping only the back porch.
    Changed file names.
2020-05-18 Removing video glitches
    Glitches occurs on VIDEN and WAIT lines due to the use of asynchronous counters 74HC4040 (the same occurs when using the 74LS393). Those gliteches are usually controlled by a filtering capacitor in t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
    Those glitches can be seen as image interference on screen while the CPU are accessing video memory.
2020-05-18 Update reflecting PCB changes
2020-06-16 Preparing for expansion
2020-06-16 PLD update for expansion
2020-06-16 PLD update
2020-06-16 Video improvement (#6)
    * Preparing for expansion
    * PLD update for expansion
    * PLD update
2020-06-16 Resizing Board
2020-06-16 production gerbers
2020-06-16 Keyboard redimensioning (#7)
    * Resizing Board
    * production gerbers
2020-06-16 production gerbers (#8)
2020-06-16 README repair
2020-06-22 Create LICENSE
2020-06-24 Update README.md
    Including technical details
2020-08-13 Added Expansion color image
2020-08-13 color expansion screen
2020-08-14 Working ROM image
2020-10-06 Added llibrary
    Added missing livrary and PDF schematic
2021-11-10 Update README.md
    https://forum.kicad.info/t/warning-avoid-all-links-to-kicad-pcb-org-use-kicad-org/31521
2021-11-14 Update README.md (#10)
    https://forum.kicad.info/t/warning-avoid-all-links-to-kicad-pcb-org-use-kicad-org/31521
